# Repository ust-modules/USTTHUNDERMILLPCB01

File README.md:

# THUNDERMILL01 stator PCB

The PCB is part of [Electric field mill](https://github.com/UniversalScientificTechnologies/THUNDERMILL01).

The PCB consists analog front end, microcontroller and interface connectors.

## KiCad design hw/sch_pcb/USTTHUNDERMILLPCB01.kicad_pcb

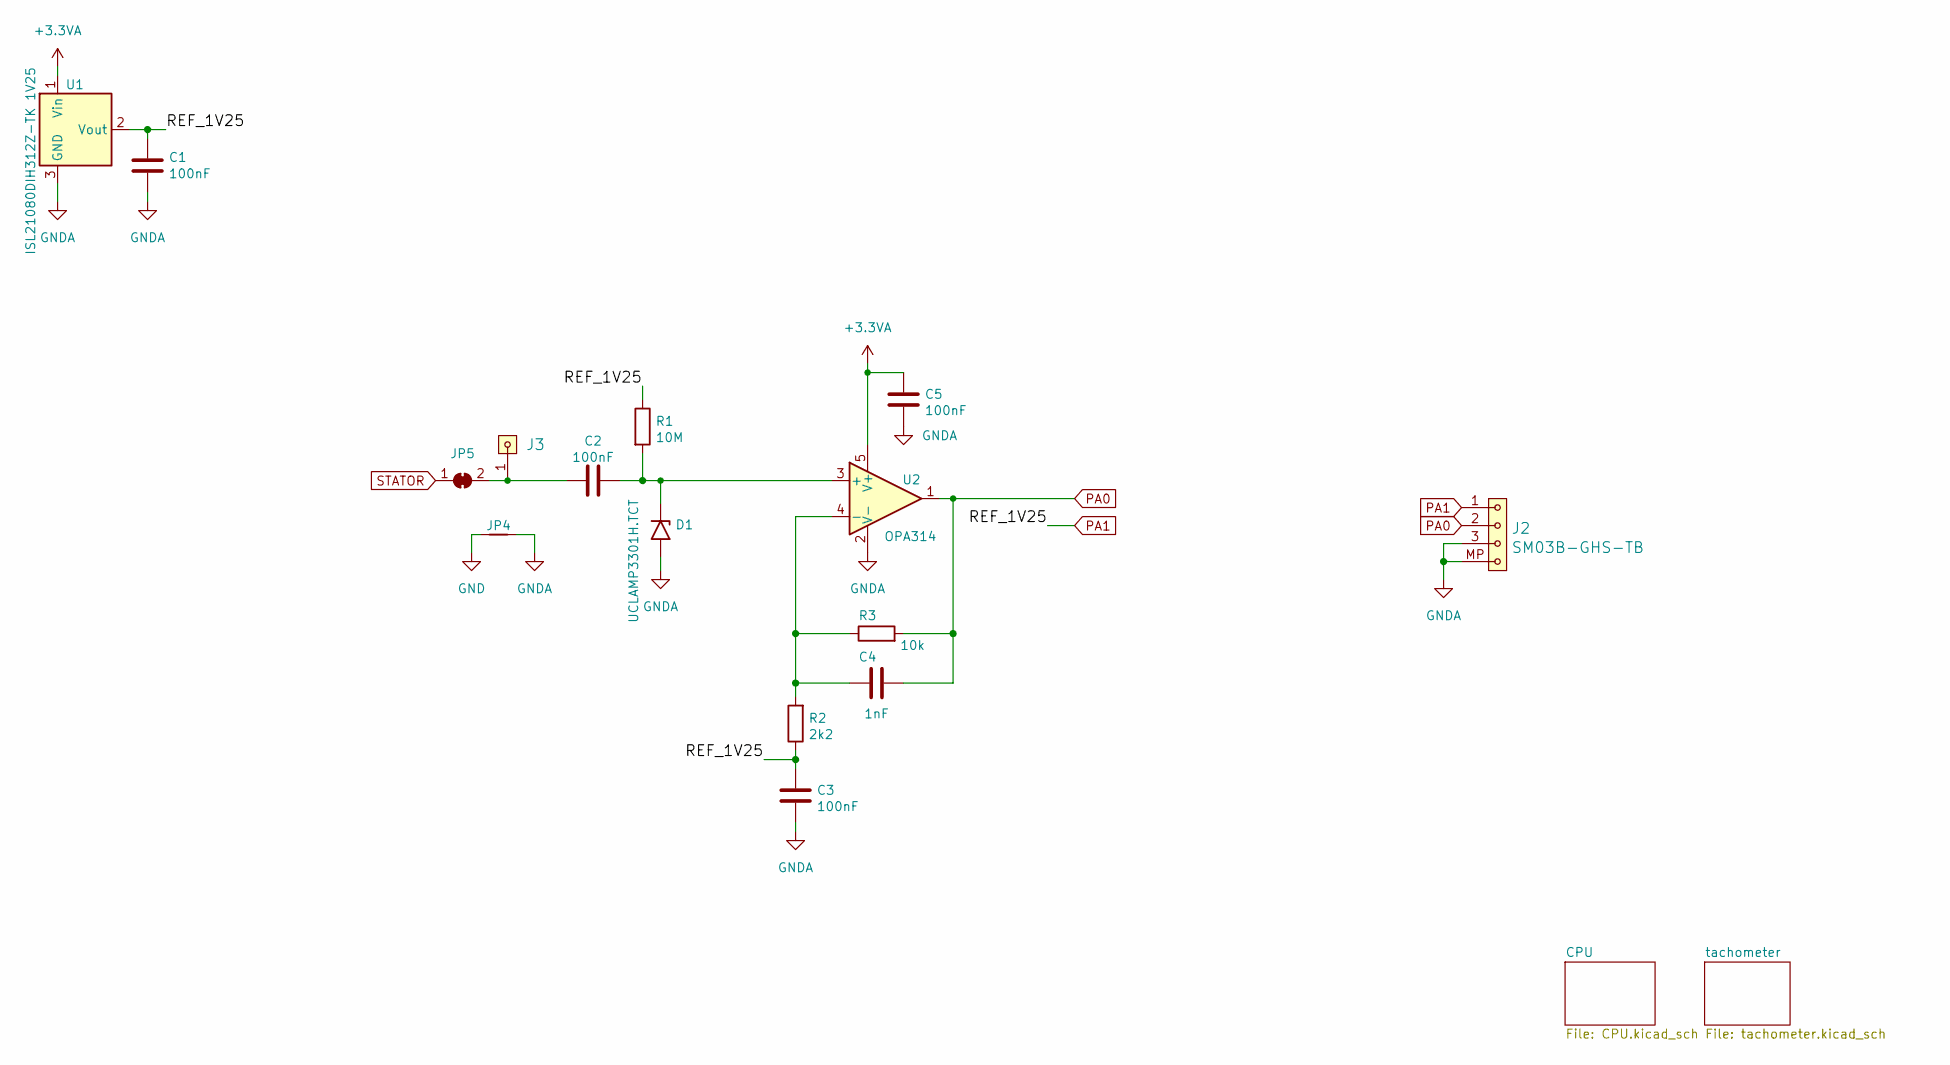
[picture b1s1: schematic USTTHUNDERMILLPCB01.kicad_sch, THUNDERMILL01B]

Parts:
C1, C2, C3, C5: 100nF; C_0603_1608Metric
C4: 1nF; C_0603_1608Metric
D1: UCLAMP3301H.TCT; D_SOD-523
J2: SM03B-GHS-TB; JST_GH_SM03B-GHS-TB_1x03-1MP_P1.25mm_Horizontal
J3: HEADER_1x01; Straight_1x01
JP4: Jumper_2_Bridged; NetTie-2_SMD_Pad0.5mm
JP5: SolderJumper_2_Bridged; SolderJumper-2_P1.3mm_Bridged_RoundedPad1.0x1.5mm
R1: 10M; R_0603_1608Metric
R2: 2k2; R_0603_1608Metric
R3: 10k; R_0603_1608Metric
U1: ISL21080DIH312Z-TK 1V25; SOT-23
U2: OPA314; SOT-23-5

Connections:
+3.3VA: C5.2, U1.1 (Vin), U2.5 (V+); also elsewhere on the board
GND: JP4.1; also elsewhere on the board
GNDA: C1.2, C3.1, C5.1, D1.2 (A2), J2.3, J2.MP, JP4.2, U1.3 (GND), U2.2 (V-); also elsewhere on the board
unnamed: C2.2, D1.1 (A1), R1.2, U2.3 (+)
unnamed: C2.1, J3.1, JP5.2 (B)
unnamed: C4.1, R2.2, R3.1, U2.4 (-)
PA0: C4.2, J2.2, R3.2, U2.1; also elsewhere on the board
PA1: C1.1, C3.2, J2.1, R1.1, R2.1, U1.2 (Vout); also elsewhere on the board
STATOR: JP5.1 (A)

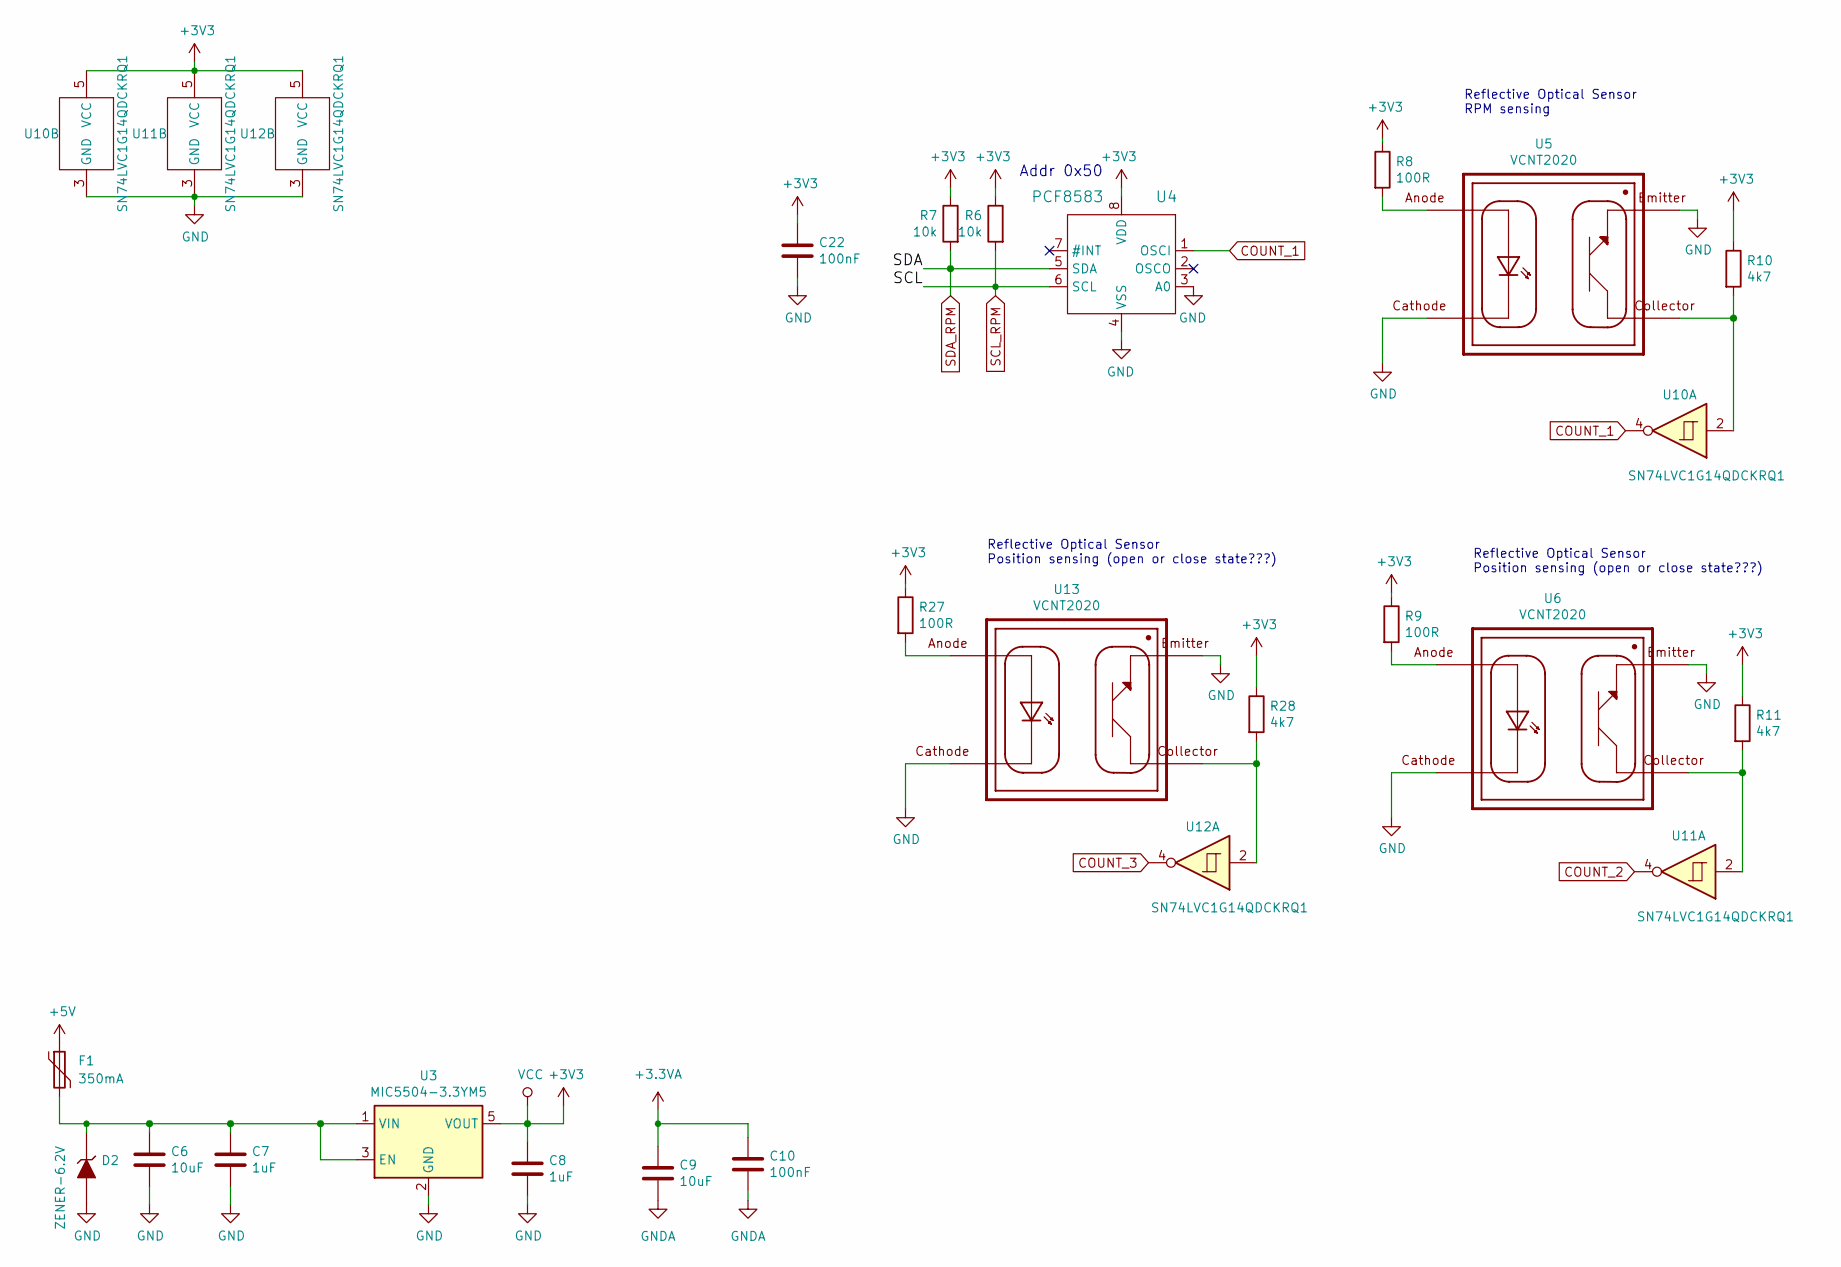
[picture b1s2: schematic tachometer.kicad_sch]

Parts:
C6, C9: 10uF; C_0805_2012Metric
C7, C8: 1uF; C_0603_1608Metric
C10, C22: 100nF; C_0603_1608Metric
D2: ZENER-6.2V; Diode-MiniMELF_Standard
F1: 350mA; Fuse_1812_4532Metric
R6, R7: 10k; R_0603_1608Metric
R8, R9, R27: 100R; R_0603_1608Metric
R10, R11, R28: 4k7; R_0603_1608Metric
U3: MIC5504-3.3YM5; SOT-23-5
U4: PCF8583; SOT176-1
U5, U6, U13: VCNT2020; XDCR_VCNT2020
U10, U11, U12: SN74LVC1G14QDCKRQ1; SOT-353_SC-70-5

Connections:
+3.3VA: C9.1, C10.1; also elsewhere on the board
+3V3: C8.1, C22.1, R6.1, R7.1, R8.1, R9.1, R10.1, R11.1, R27.1, R28.1, U3.5 (VOUT), U4.8 (VDD), U10.5 (VCC), U11.5 (VCC), U12.5 (VCC); also elsewhere on the board
+5V: F1.1; also elsewhere on the board
COUNT_1: U4.1 (OSCI), U10.4; also elsewhere on the board
COUNT_2: U11.4; also elsewhere on the board
COUNT_3: U12.4; also elsewhere on the board
GND: C6.2, C7.2, C8.2, C22.2, D2.2 (A), U3.2 (GND), U4.3 (A0), U4.4 (VSS), U5.1, U5.4, U6.1, U6.4, U10.3 (GND), U11.3 (GND), U12.3 (GND), U13.1, U13.4; also elsewhere on the board
GNDA: C9.2, C10.2; also elsewhere on the board
unnamed: C6.1, C7.1, D2.1 (K), F1.2, U3.1 (VIN), U3.3 (EN)
unnamed: R8.2, U5.3
unnamed: R9.2, U6.3
unnamed: R10.2, U5.2, U10.2
unnamed: R11.2, U6.2, U11.2
unnamed: R27.2, U13.3
unnamed: R28.2, U12.2, U13.2
SCL_RPM: R6.2, U4.6 (SCL); also elsewhere on the board
SDA_RPM: R7.2, U4.5 (SDA); also elsewhere on the board

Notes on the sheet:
Addr 0x50
Reflective Optical Sensor Position sensing (open or close state???)
Reflective Optical Sensor RPM sensing

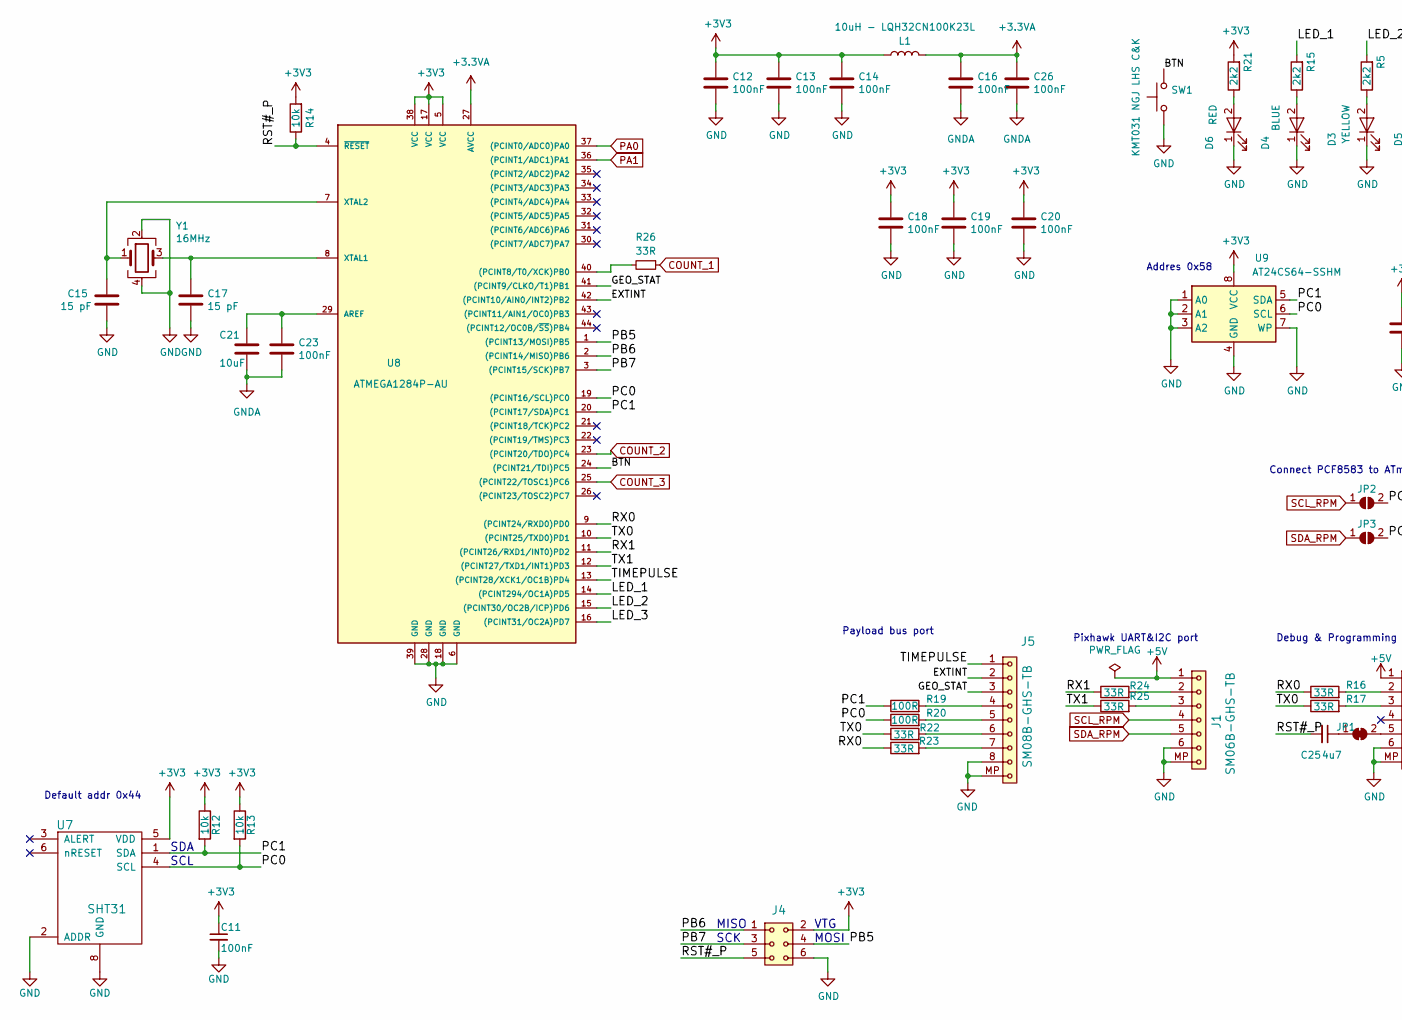
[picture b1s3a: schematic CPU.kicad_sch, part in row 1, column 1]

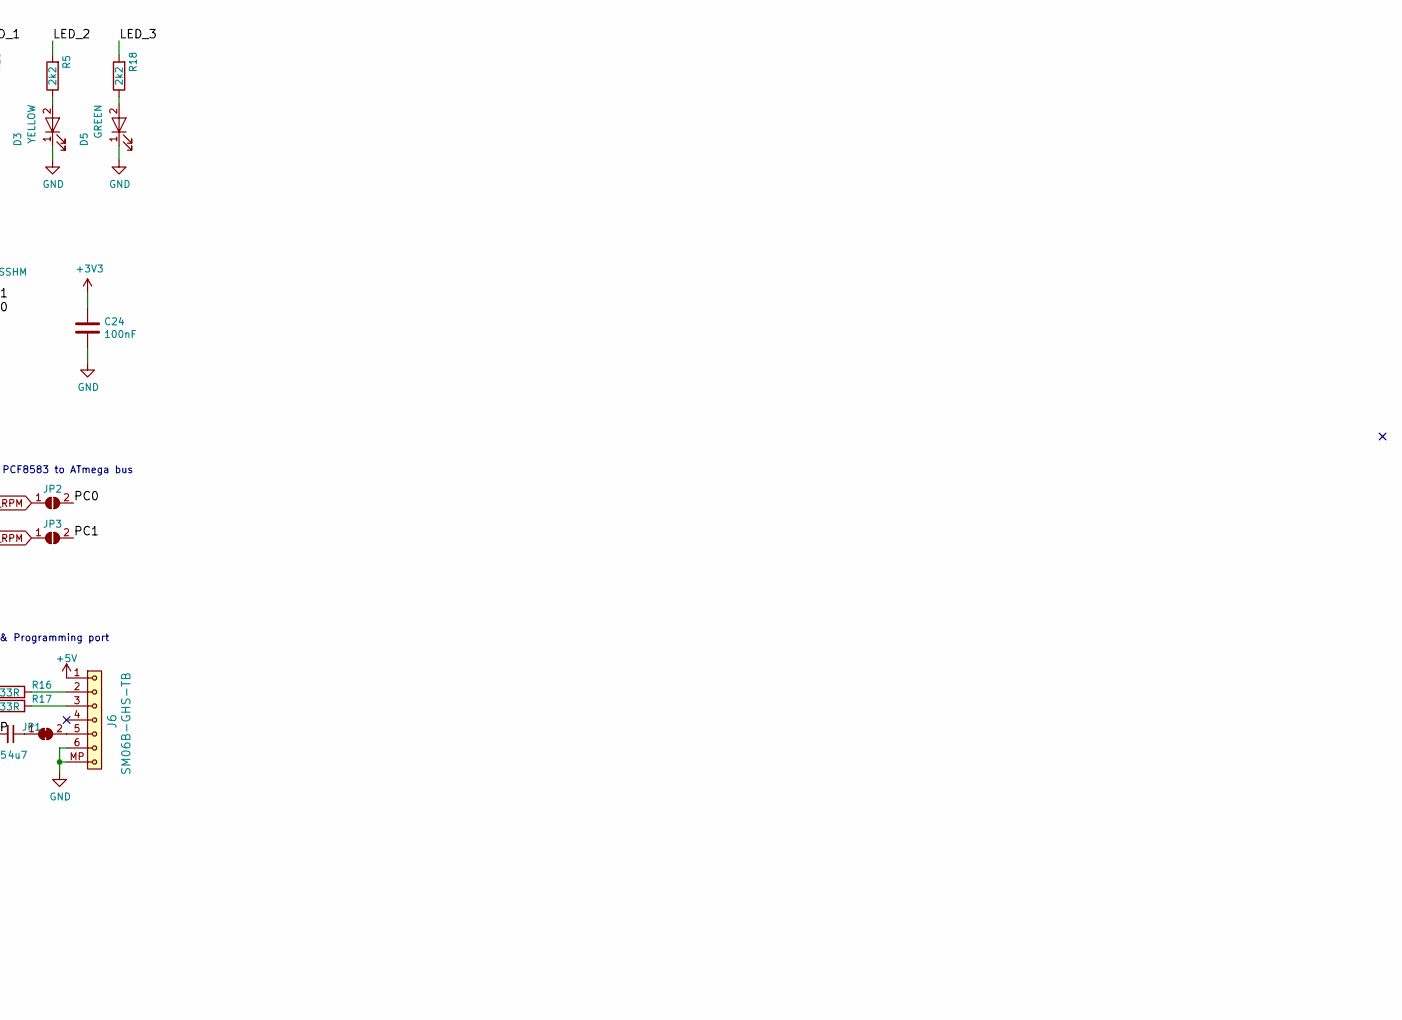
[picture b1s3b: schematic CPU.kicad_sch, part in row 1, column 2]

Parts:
C11, C12, C13, C14, C16, C18, C19, C20, C23, C24, C26: 100nF; C_0603_1608Metric
C15, C17: 15 pF; C_0603_1608Metric
C21: 10uF; C_0805_2012Metric
C25: 4u7
D3: YELLOW; LED_0603_1608Metric
D4: BLUE; LED_0603_1608Metric
D5: GREEN; LED_0603_1608Metric
D6: RED; LED_0603_1608Metric
J1, J6: SM06B-GHS-TB; JST_GH_SM06B-GHS-TB_1x06-1MP_P1.25mm_Horizontal
J4: HEADER_2x03; SMD_2x03
J5: SM08B-GHS-TB; JST_GH_SM08B-GHS-TB_1x08-1MP_P1.25mm_Horizontal
JP1: SolderJumper_2_Bridged
JP2, JP3: SolderJumper_2_Open
L1: 10uH - LQH32CN100K23L; L_1210_3225Metric
R5, R15, R18, R21: 2k2; R_0603_1608Metric
R12, R13, R14: 10k; R_0603_1608Metric
R16, R17, R22, R23, R24, R25: 33R; R_0603_1608Metric
R19, R20: 100R; R_0603_1608Metric
R26: 33R
SW1: KMT031 NGJ LHS C&K
U7: SHT31; DFN-8-1EP_2.4x2.4mm_Pitch0.5mm
U8: ATMEGA1284P-AU; TQFP-44_10x10mm_P0.8mm
U9: AT24CS64-SSHM; SOIC-8_3.9x4.9mm_P1.27mm
Y1: 16MHz; Crystal SMD CFPX-180

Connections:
+3.3VA: C16.1, C26.1, L1.2, U8.27 (AVCC); also elsewhere on the board
+3V3: C11.1, C12.1, C13.1, C14.1, C18.1, C19.1, C20.1, C24.1, J4.2, L1.1, R12.1, R13.1, R14.2, R21.2, U7.5 (VDD), U8.5 (VCC), U8.17 (VCC), U8.38 (VCC), U9.8 (VCC); also elsewhere on the board
+5V: J1.1, J6.1; also elsewhere on the board
/CPU/BTN: SW1.2, U8.24 ((PCINT21/TDI)PC5)
/CPU/EXTINT: J5.2, U8.42 ((PCINT10/AIN0/INT2)PB2)
/CPU/GEO_STAT: J5.3, U8.41 ((PCINT9/CLKO/T1)PB1)
/CPU/LED_1: R15.2, U8.14 ((PCINT294/OC1A)PD5)
/CPU/LED_2: R5.2, U8.15 ((PCINT30/OC2B/ICP)PD6)
/CPU/LED_3: R18.2, U8.16 ((PCINT31/OC2A)PD7)
/CPU/PB5: J4.4, U8.1 ((PCINT13/MOSI)PB5)
/CPU/PB6: J4.1, U8.2 ((PCINT14/MISO)PB6)
/CPU/PB7: J4.3, U8.3 ((PCINT15/SCK)PB7)
/CPU/PC0: JP2.2 (B), R13.2, R20.1, U7.4 (SCL), U8.19 ((PCINT16/SCL)PC0), U9.6 (SCL)
/CPU/PC1: JP3.2 (B), R12.2, R19.1, U7.1 (SDA), U8.20 ((PCINT17/SDA)PC1), U9.5 (SDA)
/CPU/RST#_P: C25.2, J4.5, R14.1, U8.4 (~RESET)
/CPU/RX0: R16.1, R23.1, U8.9 ((PCINT24/RXD0)PD0)
/CPU/RX1: R24.1, U8.11 ((PCINT26/RXD1/INT0)PD2)
/CPU/TIMEPULSE: J5.1, U8.13 ((PCINT28/XCK1/OC1B)PD4)
/CPU/TX0: R17.1, R22.1, U8.10 ((PCINT25/TXD0)PD1)
/CPU/TX1: R25.1, U8.12 ((PCINT27/TXD1/INT1)PD3)
COUNT_1: R26.1; also elsewhere on the board
COUNT_2: U8.23 ((PCINT20/TDO)PC4); also elsewhere on the board
COUNT_3: U8.25 ((PCINT22/TOSC1)PC6); also elsewhere on the board
GND: C11.2, C12.2, C13.2, C14.2, C15.2, C17.2, C18.2, C19.2, C20.2, C24.2, D3.1 (K), D4.1 (K), D5.1 (K), D6.1 (K), J1.6, J1.MP, J4.6, J5.8, J5.MP, J6.6, J6.MP, SW1.1, U7.2 (ADDR), U7.7 (GND), U7.8 (GND), U7.9 (GND), U8.6 (GND), U8.18 (GND), U8.28 (GND), U8.39 (GND), U9.1 (A0), U9.2 (A1), U9.3 (A2), U9.4 (GND), U9.7 (WP), Y1.2, Y1.4; also elsewhere on the board
GNDA: C16.2, C21.2, C23.2, C26.2; also elsewhere on the board
unnamed: D3.2 (A), R5.1
unnamed: D4.2 (A), R15.1
unnamed: D5.2 (A), R18.1
unnamed: D6.2 (A), R21.1
unnamed: J1.2, R24.2
unnamed: J1.3, R25.2
unnamed: J5.4, R19.2
unnamed: J5.5, R20.2
unnamed: J5.6, R22.2
unnamed: J5.7, R23.2
unnamed: J6.2, R16.2
unnamed: J6.3, R17.2
unnamed: C25.1, JP1.1 (A)
unnamed: J6.5, JP1.2 (B)
unnamed: R26.2, U8.40 ((PCINT8/T0/XCK)PB0)
unnamed: C21.1, C23.1, U8.29 (AREF)
unnamed: C17.1, U8.8 (XTAL1), Y1.3
unnamed: C15.1, U8.7 (XTAL2), Y1.1
PA0: U8.37 ((PCINT0/ADC0)PA0); also elsewhere on the board
PA1: U8.36 ((PCINT1/ADC1)PA1); also elsewhere on the board
SCL_RPM: J1.4, JP2.1 (A); also elsewhere on the board
SDA_RPM: J1.5, JP3.1 (A); also elsewhere on the board

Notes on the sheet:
VTG
MISO
SCL
Default addr 0x44
MOSI
SDA
Payload bus port
Connect PCF8583 to ATmega bus
Debug & Programming port
SCK
Pixhawk UART&I2C port
Addres 0x58

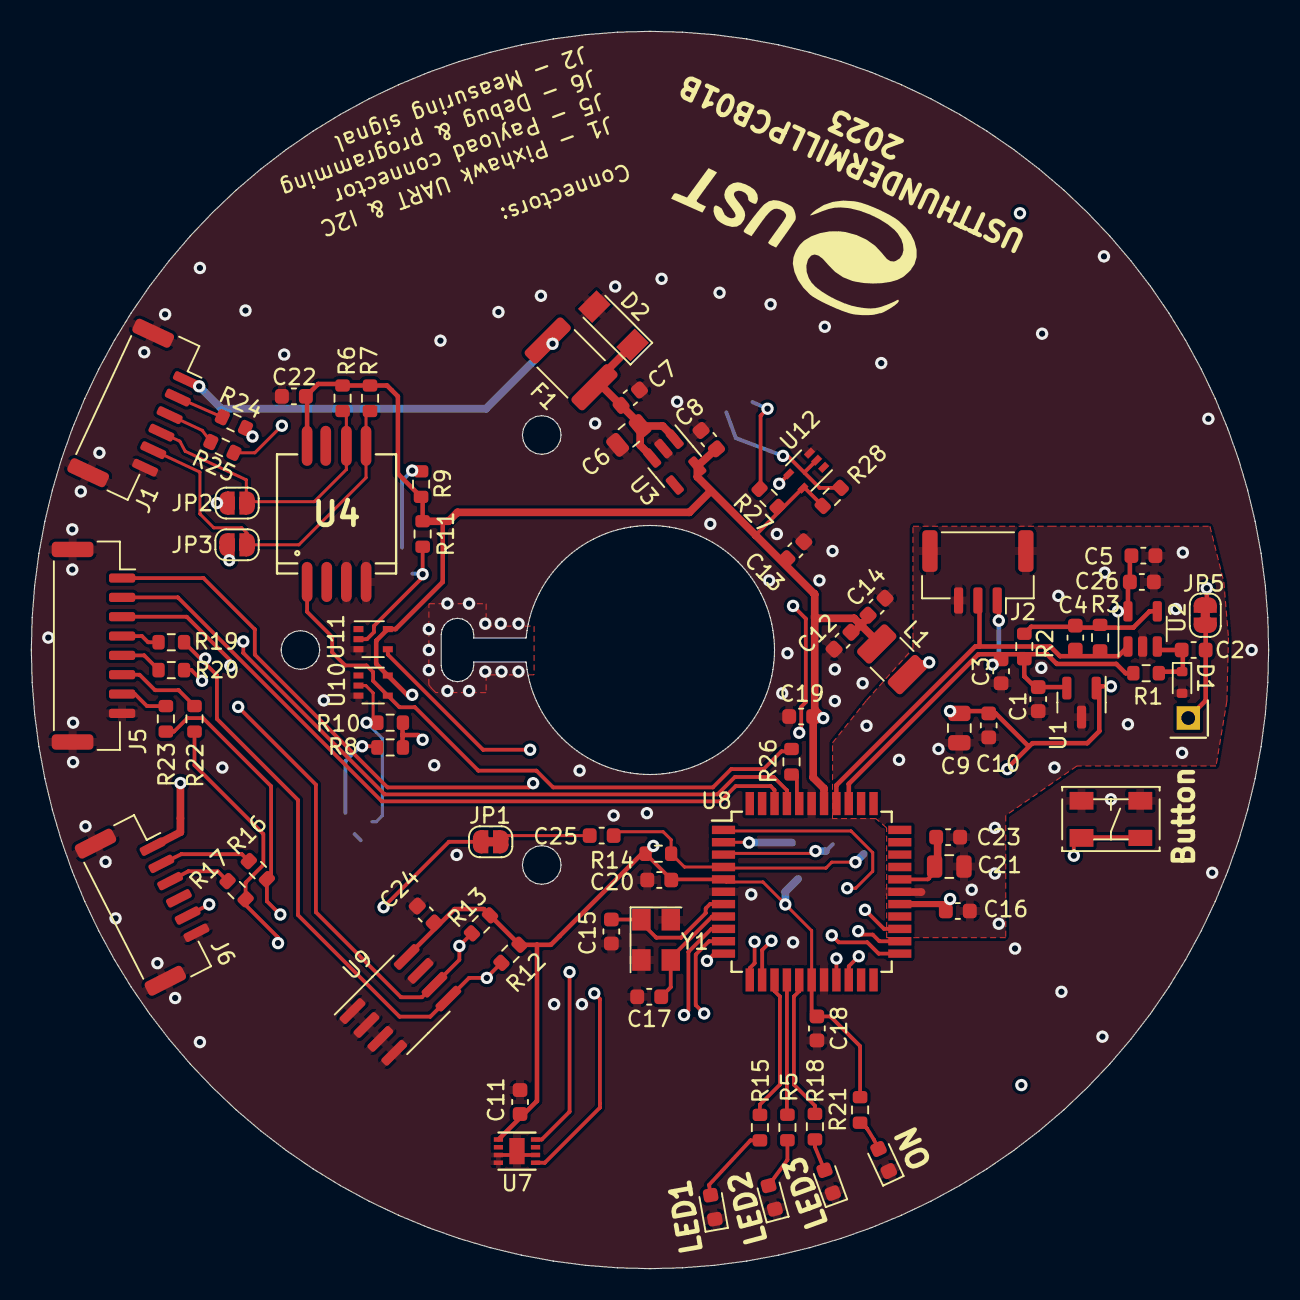
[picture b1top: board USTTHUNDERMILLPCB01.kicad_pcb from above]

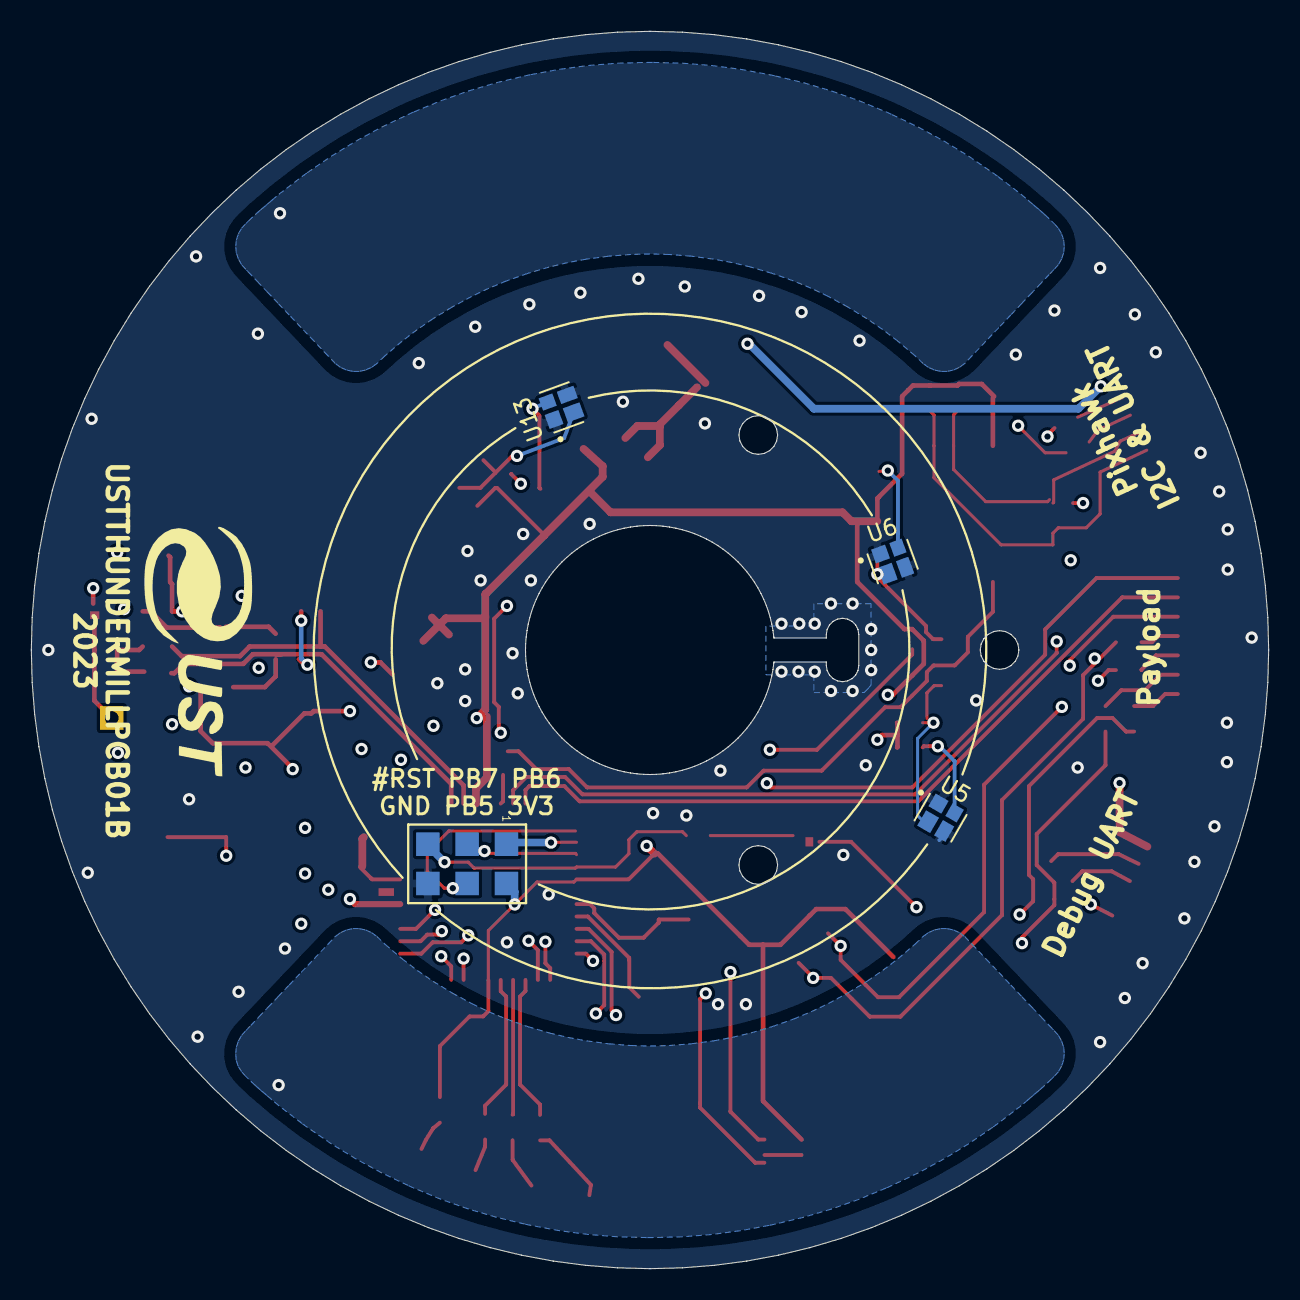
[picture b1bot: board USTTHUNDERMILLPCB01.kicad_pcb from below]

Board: 4 copper layers, 80.0 x 80.0 mm, 89 parts (5 on the bottom side), 57 nets.

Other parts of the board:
G1, G2: UST

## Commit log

2023-06-13 Update actions products
2023-07-04 Editing component values
2023-07-04 Editing F. and B.FAB
2023-11-04 Updated title block.
2025-02-15 Update project to KiCADv8.
